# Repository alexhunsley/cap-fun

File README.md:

# cap-fun

I made this to try out KiCad, see [blog post](https://hunsley.io/posts/2025/electronics-kicad-pcb-fabrication-cap-fun) and [follow-up](https://hunsley.io/posts/2025/electronics-cap-fun-pcb-fabrication-result-jlcpcb/).

This is a small educational circuit for demonstrating how capacitors work:

* insert an electrolytic capacitor (I suggest `1000uF`) into the cap header (longer leg goes next to the `+` symbol)
* insert a 3mm red LED into the LED header (longer leg goes next to the `+` symbol)

Now hold down the `discharge` push button. If the cap has charge, the LED should light and fade as the cap discharges.

If you want to be able to charge the cap, connect the `+V` and `GND` pads to a DC power source (5V suggested), and the `charge` push button will charge the cap while it is held down.

More info at [blog post](https://hunsley.io/posts/2025/electronics-kicad-pcb-fabrication-cap-fun).

## Footnotes

* the cap voltage rating doesn't matter much because it can only charge up to the voltage the power supply provides

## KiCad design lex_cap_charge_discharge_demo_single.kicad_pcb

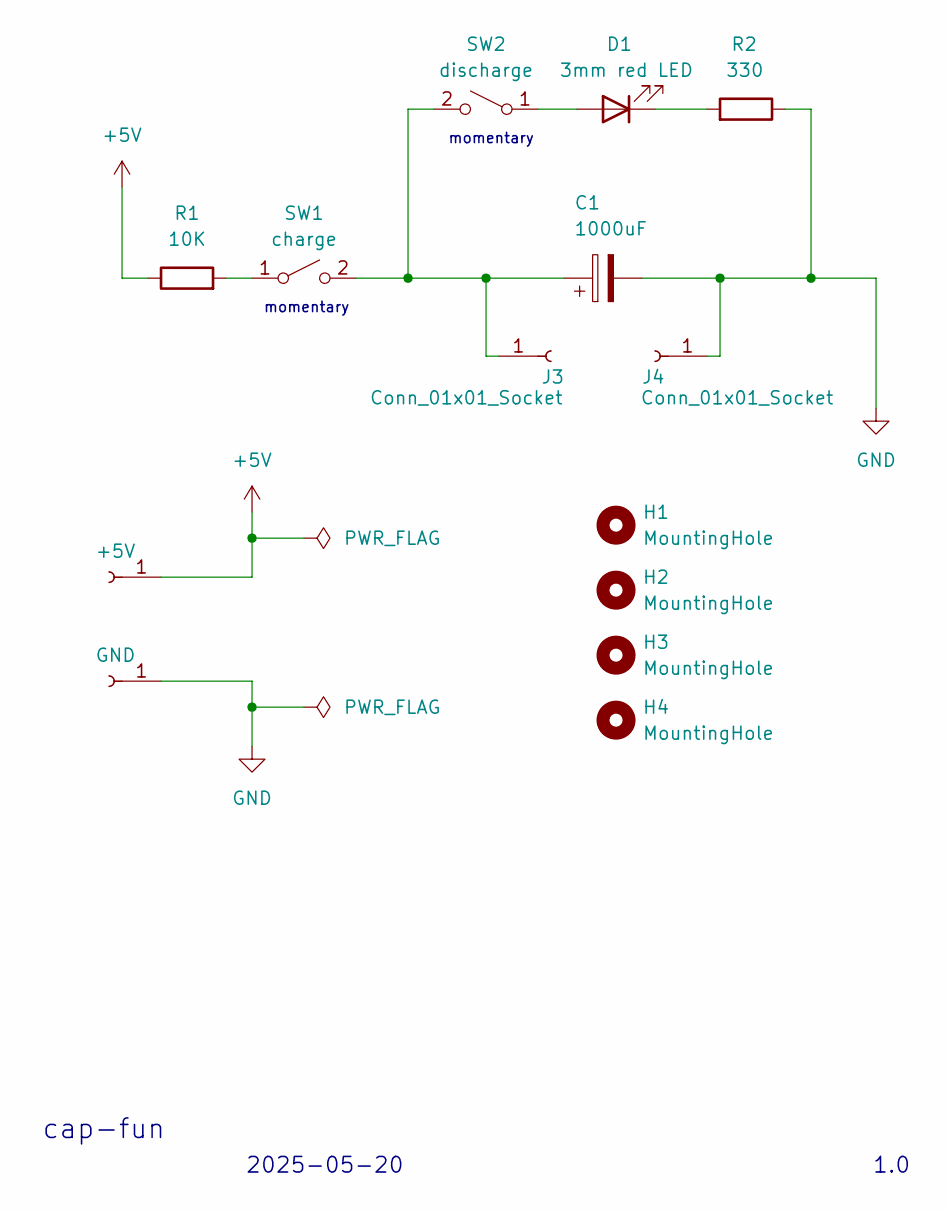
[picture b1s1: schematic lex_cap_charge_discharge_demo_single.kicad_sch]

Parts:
C1: 1000uF; CP_Radial_D10.0mm_P5.00mm
D1: 3mm red LED; LED_D3.0mm
H1, H2, H3, H4: MountingHole; MountingHole_2.2mm_M2
J1: +5V; TestPoint_THTPad_2.5x2.5mm_Drill1.2mm
J2: GND; TestPoint_THTPad_2.5x2.5mm_Drill1.2mm
J3, J4: Conn_01x01_Socket; PinSocket_1x01_P2.54mm_Vertical
R1: 10K; R_Axial_DIN0204_L3.6mm_D1.6mm_P7.62mm_Horizontal
R2: 330; R_Axial_DIN0204_L3.6mm_D1.6mm_P7.62mm_Horizontal
SW1: charge; SW_PUSH_6mm_H4.3mm
SW2: discharge; SW_PUSH_6mm_H4.3mm

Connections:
+5V: J1.1, R1.1
GND: C1.2, J2.1, J4.1, R2.1
unnamed: D1.2 (A), SW2.1 (A)
unnamed: D1.1 (K), R2.2
unnamed: C1.1, J3.1, SW1.2 (B), SW2.2 (B)
unnamed: R1.2, SW1.1 (A)

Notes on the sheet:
1.0
momentary
2025-05-20
cap-fun

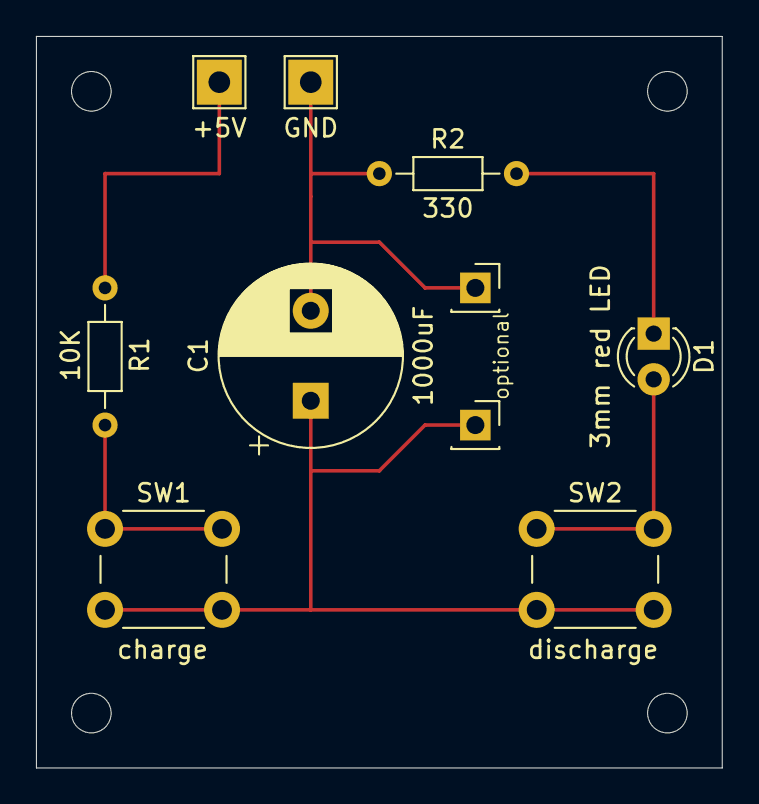
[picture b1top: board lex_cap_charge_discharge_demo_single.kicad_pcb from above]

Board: 2 copper layers, 38.1 x 40.6 mm, 14 parts (0 on the bottom side), 6 nets.

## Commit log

2025-05-17 Churn
2025-05-17 Add cap-fun demo single files
2025-05-17 Add README
2025-05-17 put resistor next to +5v, tidy
2025-05-17 Tweak R vals
2025-05-20 Change various incl +V, GND solder pads; move components to 0.24mm standard pitch grid; add text front/back
2025-05-20 Put track across connected switch pins:
    to keep kiCad ERC happy. Also more forgiving of a switch pin joint failure.
    Apparently if I just ignored the warning it would be fine too.
2025-05-20 Tweak, add title
2025-05-20 Convert to A5 size (was A4)
2025-05-20 Tweaks. This is what's in blog post.
2025-05-20 Put rev. 1.0 on schematic sheet info box
2025-05-21 Add 2.2mm mounting holes at corners (made board bigger)
2025-05-21 Fillet (round) corners by 3mm, tweak front title text size
2025-05-21 Move grid origin to new top left of board
2025-05-21 tidy-up mounting holes position in sch
2025-05-26 Add optional component (with header) around cap
2025-05-26 Add optional text at header points for it
2025-05-26 Make board bigger (4cm x 4cm), fix SMD cap to THT
2025-05-26 add hunsley.io top of front, make optional headers closer to cap
2025-05-27 Add order 1 (JCLPCB), just placed, 75 pieces in 5 panels (3x5 plus rails per panel)
2025-05-27 Remake gerber zip with empty paste files removed
2025-05-27 Fix missing 1000uF silk text for the cap (d'oh)
2025-06-05 Add some viewport presets for making blog screenshots
